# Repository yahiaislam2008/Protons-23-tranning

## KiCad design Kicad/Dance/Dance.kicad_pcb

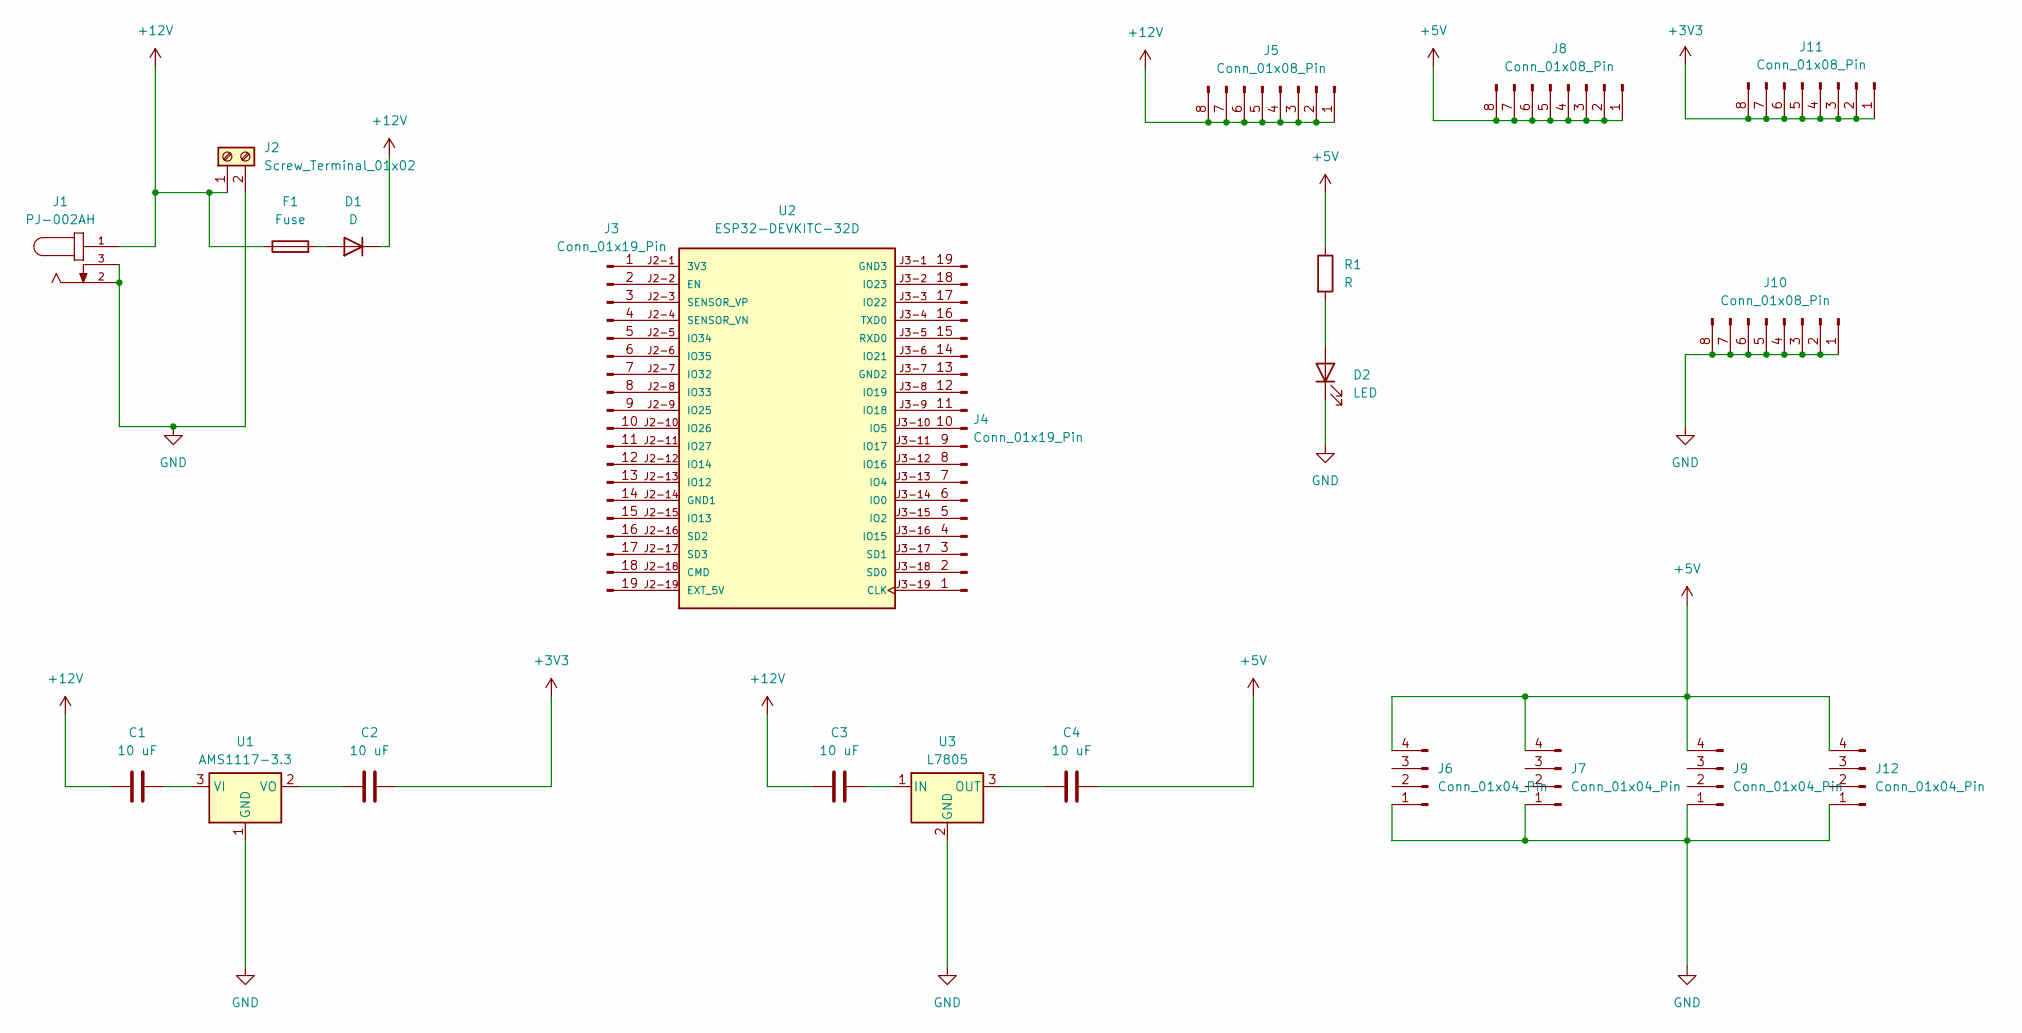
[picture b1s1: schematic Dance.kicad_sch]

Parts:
C1, C2, C3, C4: 10 uF; C_Axial_L3.8mm_D2.6mm_P10.00mm_Horizontal
D1: D; D_5KPW_P12.70mm_Horizontal
D2: LED; LED_D3.0mm
F1: Fuse; Fuse_BelFuse_0ZRE0005FF_L8.3mm_W3.8mm
J1: PJ-002AH; CUI_PJ-002AH
J2: Screw_Terminal_01x02; TerminalBlock_Phoenix_MKDS-1,5-2-5.08_1x02_P5.08mm_Horizont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
J3, J4: Conn_01x19_Pin; PinHeader_1x19_P2.54mm_Vertical
J5, J8, J10, J11: Conn_01x08_Pin; PinHeader_1x08_P2.00mm_Vertical
J6, J7, J9, J12: Conn_01x04_Pin; PinHeader_1x04_P2.00mm_Vertical
R1: R; R_Axial_DIN0207_L6.3mm_D2.5mm_P7.62mm_Horizontal
U1: AMS1117-3.3; SOT-223-3_TabPin2
U2: ESP32-DEVKITC-32D; MODULE_ESP32-DEVKITC-32D; PARTREV V4
U3: L7805; TO-220-3_Vertical

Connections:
+3V3: C2.2, J11.1, J11.2, J11.3, J11.4, J11.5, J11.6, J11.7, J11.8
+5V: C4.2, J6.4, J7.4, J8.1, J8.2, J8.3, J8.4, J8.5, J8.6, J8.7, J8.8, J9.4, J12.4, R1.1
+12V: C1.1, C3.1, D1.1 (K), F1.1, J1.1, J2.1, J5.1, J5.2, J5.3, J5.4, J5.5, J5.6, J5.7, J5.8
GND: D2.1 (K), J1.2, J1.3, J2.2, J6.1, J7.1, J9.1, J10.1, J10.2, J10.3, J10.4, J10.5, J10.6, J10.7, J10.8, J12.1, U1.1 (GND), U3.2 (GND)
unnamed: D1.2 (A), F1.2
unnamed: D2.2 (A), R1.2
unnamed: J3.1, U2.J2-1 (3V3)
unnamed: J3.2, U2.J2-2 (EN)
unnamed: J3.3, U2.J2-3 (SENSOR_VP)
unnamed: J3.4, U2.J2-4 (SENSOR_VN)
unnamed: J3.5, U2.J2-5 (IO34)
unnamed: J3.6, U2.J2-6 (IO35)
unnamed: J3.7, U2.J2-7 (IO32)
unnamed: J3.8, U2.J2-8 (IO33)
unnamed: J3.9, U2.J2-9 (IO25)
unnamed: J3.10, U2.J2-10 (IO26)
unnamed: J3.11, U2.J2-11 (IO27)
unnamed: J3.12, U2.J2-12 (IO14)
unnamed: J3.13, U2.J2-13 (IO12)
unnamed: J3.14, U2.J2-14 (GND1)
unnamed: J3.15, U2.J2-15 (IO13)
unnamed: J3.16, U2.J2-16 (SD2)
unnamed: J3.17, U2.J2-17 (SD3)
unnamed: J3.18, U2.J2-18 (CMD)
unnamed: J3.19, U2.J2-19 (EXT_5V)
unnamed: J4.1, U2.J3-19 (CLK)
unnamed: J4.2, U2.J3-18 (SD0)
unnamed: J4.3, U2.J3-17 (SD1)
unnamed: J4.4, U2.J3-16 (IO15)
unnamed: J4.5, U2.J3-15 (IO2)
unnamed: J4.6, U2.J3-14 (IO0)
unnamed: J4.7, U2.J3-13 (IO4)
unnamed: J4.8, U2.J3-12 (IO16)
unnamed: J4.9, U2.J3-11 (IO17)
unnamed: J4.10, U2.J3-10 (IO5)
unnamed: J4.11, U2.J3-9 (IO18)
unnamed: J4.12, U2.J3-8 (IO19)
unnamed: J4.13, U2.J3-7 (GND2)
unnamed: J4.14, U2.J3-6 (IO21)
unnamed: J4.15, U2.J3-5 (RXD0)
unnamed: J4.16, U2.J3-4 (TXD0)
unnamed: J4.17, U2.J3-3 (IO22)
unnamed: J4.18, U2.J3-2 (IO23)
unnamed: J4.19, U2.J3-1 (GND3)
unnamed: C1.2, U1.3 (VI)
unnamed: C2.1, U1.2 (VO)
unnamed: C3.2, U3.1 (IN)
unnamed: C4.1, U3.3 (OUT)

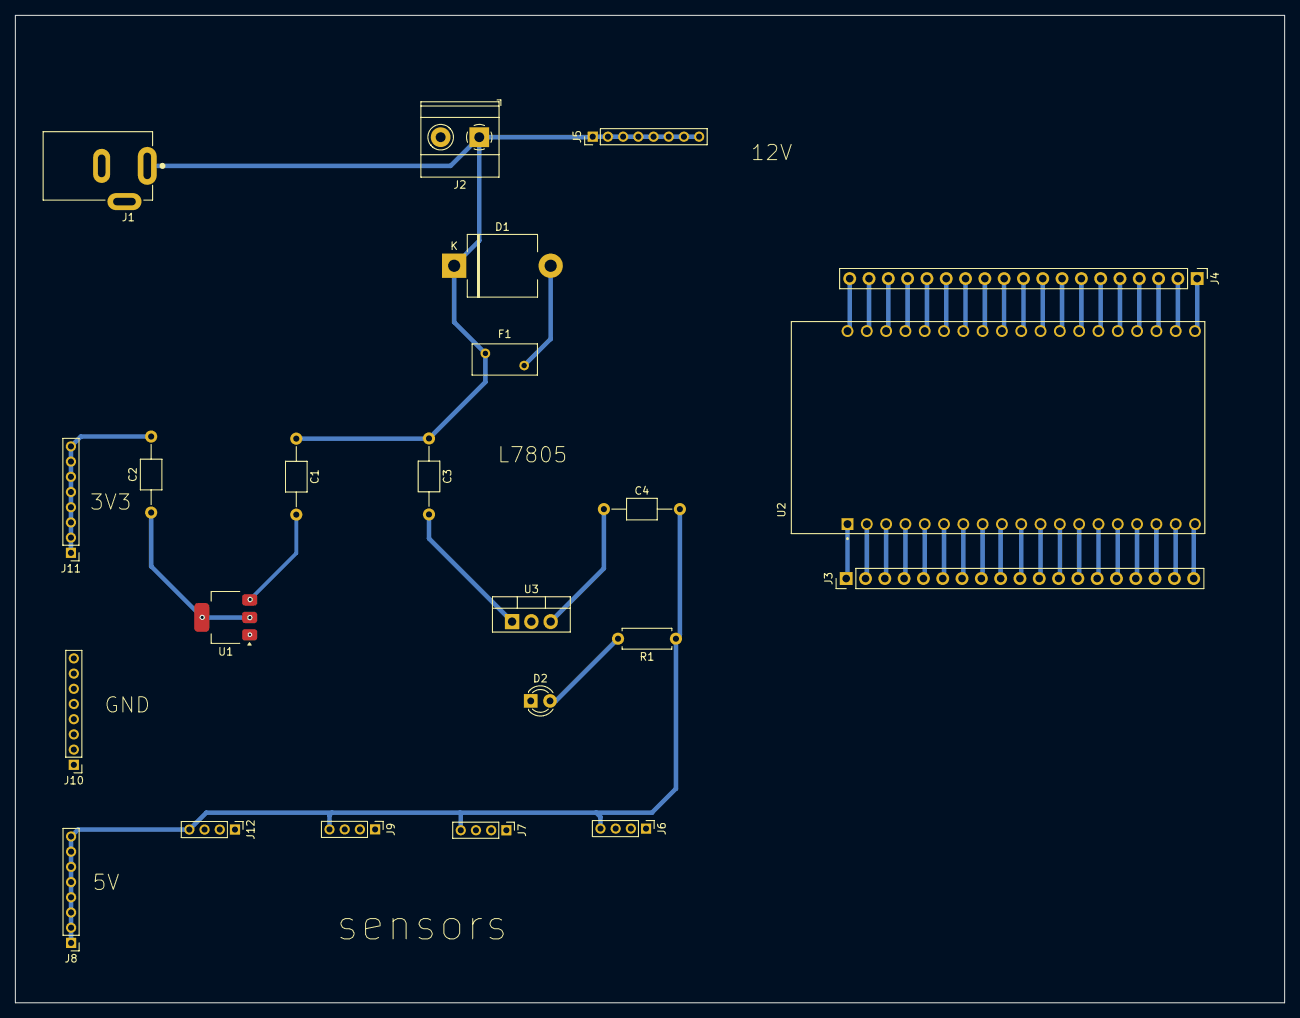
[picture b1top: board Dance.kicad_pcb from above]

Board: 2 copper layers, 167.0 x 129.9 mm, 23 parts (0 on the bottom side), 48 nets.

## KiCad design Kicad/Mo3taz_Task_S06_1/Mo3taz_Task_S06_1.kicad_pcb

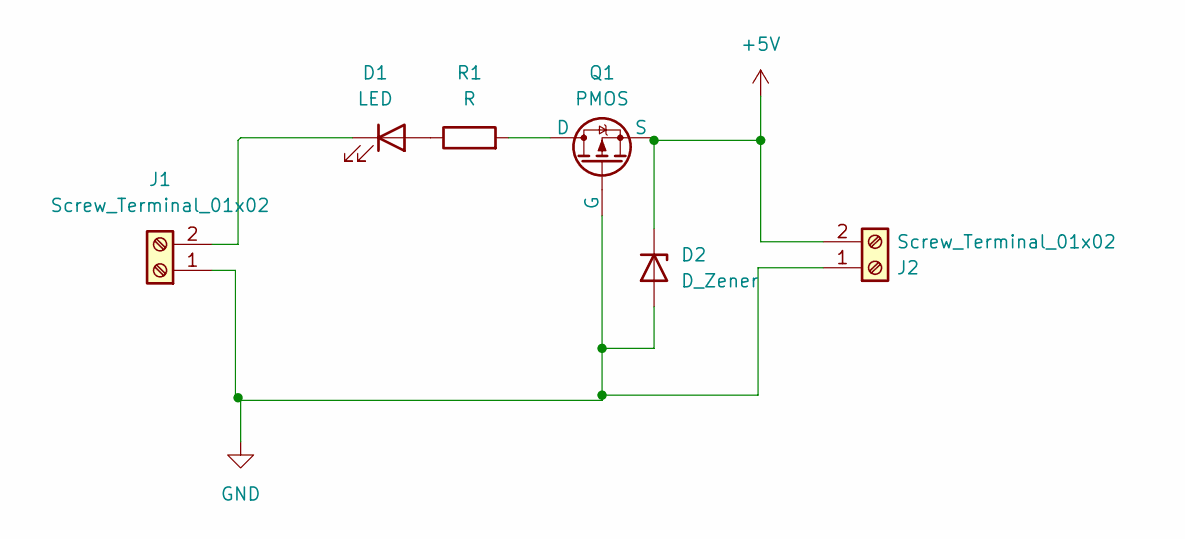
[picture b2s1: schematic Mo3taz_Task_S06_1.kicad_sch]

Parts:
D1: LED; LED_0603_1608Metric
D2: D_Zener; D_0603_1608Metric
J1, J2: Screw_Terminal_01x02; TerminalBlock_Phoenix_MKDS-1,5-2-5.08_1x02_P5.08mm_Horizont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
Q1: PMOS; GaN_Systems_GaNPX-3_5x6.6mm_Drain2.93x0.6mm
R1: R; R_0603_1608Metric

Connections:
+5V: D2.1 (K), J2.2, Q1.3 (S)
GND: D2.2 (A), J1.1, J2.1, Q1.2 (G)
unnamed: D1.2 (A), R1.1
unnamed: D1.1 (K), J1.2
unnamed: Q1.1 (D), R1.2

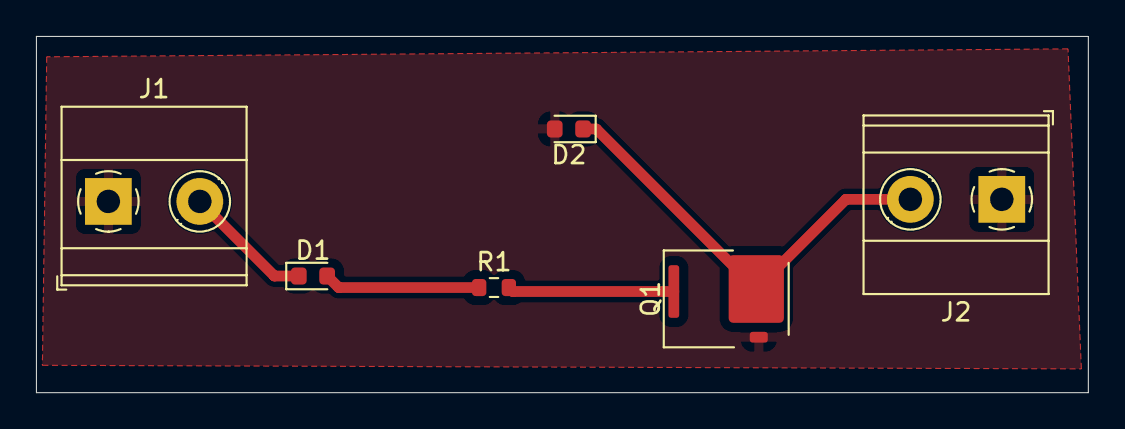
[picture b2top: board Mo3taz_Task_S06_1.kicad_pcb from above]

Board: 2 copper layers, 58.4 x 19.8 mm, 6 parts (0 on the bottom side), 5 nets.

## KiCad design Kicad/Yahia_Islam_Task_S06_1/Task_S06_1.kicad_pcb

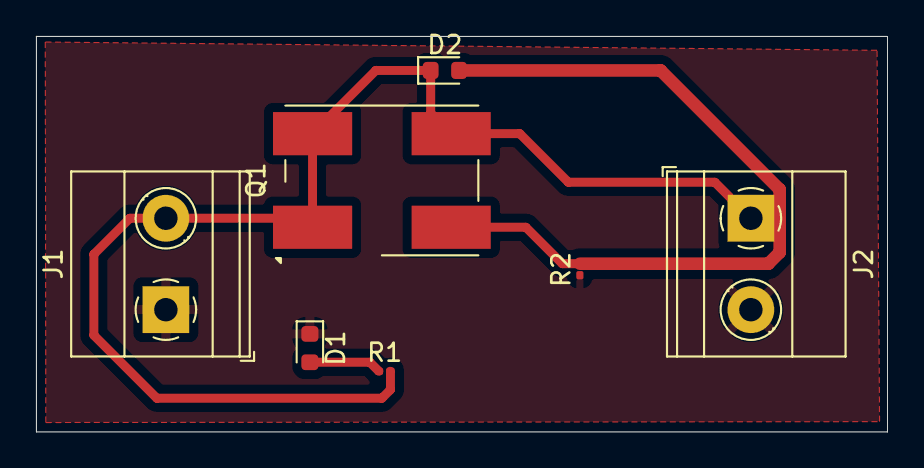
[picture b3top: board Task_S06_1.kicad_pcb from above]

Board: 2 copper layers, 47.3 x 22.0 mm, 7 parts (0 on the bottom side), 4 nets.

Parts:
D1: LED; LED_0603_1608Metric
D2: D; D_0603_1608Metric
J1, J2: Screw_Terminal_01x02; TerminalBlock_Phoenix_MKDS-1,5-2-5.08_1x02_P5.08mm_Horizont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
Q1: PMOS_Substrate; Diode_Bridge_Bourns_CD-DF4xxS
R1, R2: 330R; R_0201_0603Metric

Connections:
+9V: D2.1 (K), J1.2, J2.1, Q1.1 (D), Q1.3 (S), Q1.4 (Bulk), R1.2
GND: D1.1 (K), J1.1, J2.2, R2.1
unnamed: D1.2 (A), R1.1
unnamed: D2.2 (A), Q1.2 (G), R2.2

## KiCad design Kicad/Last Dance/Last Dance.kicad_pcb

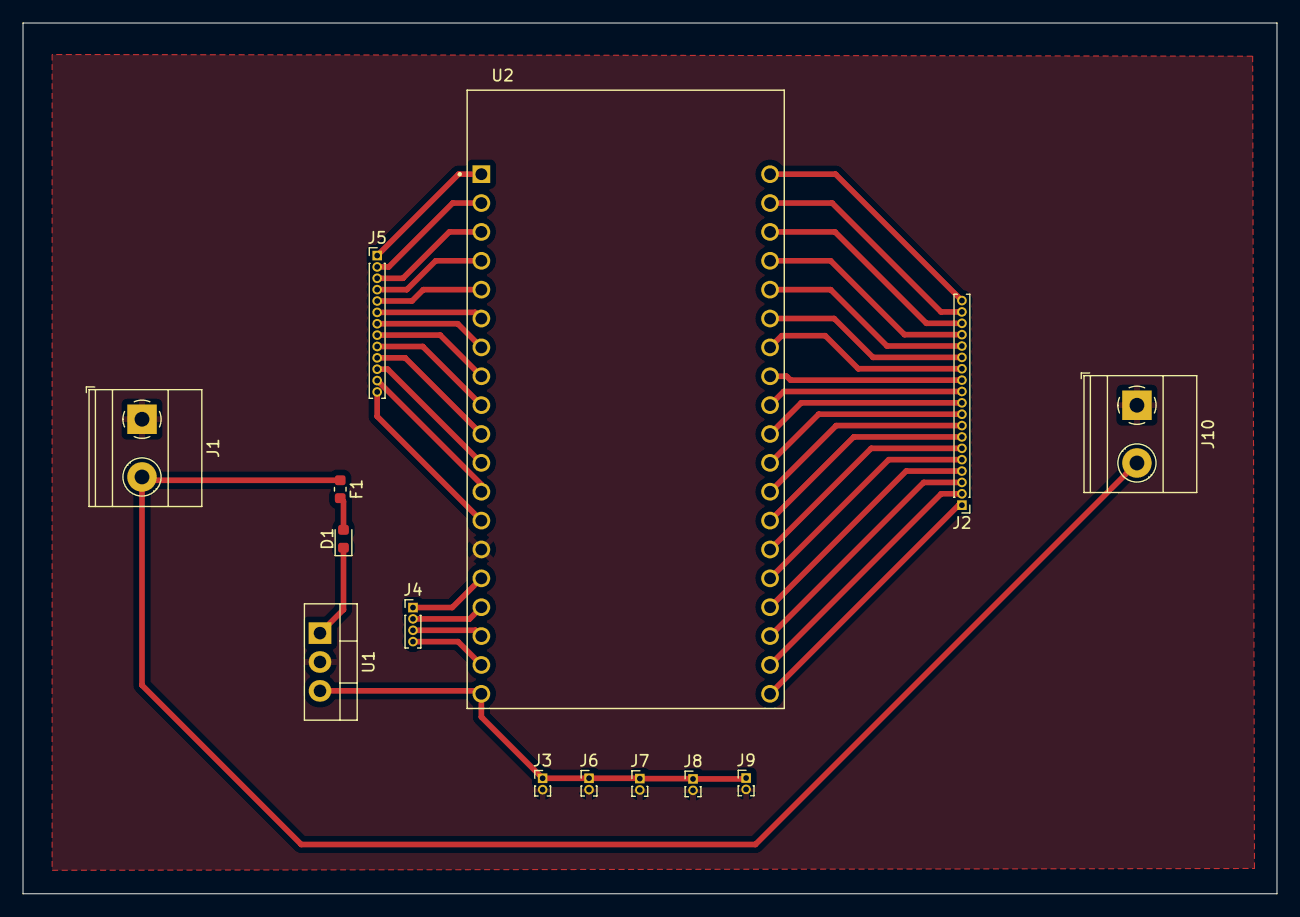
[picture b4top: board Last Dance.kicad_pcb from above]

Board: 2 copper layers, 110.3 x 76.6 mm, 14 parts (0 on the bottom side), 41 nets.

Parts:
D1: D; D_0603_1608Metric
F1: Fuse; Fuse_0603_1608Metric
J1, J10: Screw_Terminal_01x02; TerminalBlock_Phoenix_MKDS-1,5-2-5.08_1x02_P5.08mm_Horizont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
J2: Conn_01x19_Pin; PinHeader_1x19_P1.00mm_Vertical
J3, J6, J7, J8, J9: Conn_01x02_Pin; PinHeader_1x02_P1.00mm_Vertical
J4: Conn_01x04_Pin; PinHeader_1x04_P1.00mm_Vertical
J5: Conn_01x13_Pin; PinHeader_1x13_P1.00mm_Vertical
U1: LM7805_TO220; TO-220-3_Vertical
U2: ESP32-DEVKITC-32D; MODULE_ESP32-DEVKITC-32D

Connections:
+12V: F1.1, J1.2, J10.2
GND: J1.1, J3.2, J6.2, J7.2, J8.2, J9.2, J10.1, U1.2 (GND), U2.J2-14 (GND1)
unnamed: D1.2 (A), F1.2
unnamed: D1.1 (K), U1.1 (VI)
unnamed: J2.1, U2.J3-19 (CLK)
unnamed: J2.2, U2.J3-18 (SD0)
unnamed: J2.3, U2.J3-17 (SD1)
unnamed: J2.4, U2.J3-16 (IO15)
unnamed: J2.5, U2.J3-15 (IO2)
unnamed: J2.6, U2.J3-14 (IO0)
unnamed: J2.7, U2.J3-13 (IO4)
unnamed: J2.8, U2.J3-12 (IO16)
unnamed: J2.9, U2.J3-11 (IO17)
unnamed: J2.10, U2.J3-10 (IO5)
unnamed: J2.11, U2.J3-9 (IO18)
unnamed: J2.12, U2.J3-8 (IO19)
unnamed: J2.13, U2.J3-7 (GND2)
unnamed: J2.14, U2.J3-6 (IO21)
unnamed: J2.15, U2.J3-5 (RXD0)
unnamed: J2.16, U2.J3-4 (TXD0)
unnamed: J2.17, U2.J3-3 (IO22)
unnamed: J2.18, U2.J3-2 (IO23)
unnamed: J2.19, U2.J3-1 (GND3)
unnamed: J3.1, J6.1, J7.1, J8.1, J9.1, U1.3 (VO), U2.J2-19 (EXT_5V)
unnamed: J4.1, U2.J2-15 (IO13)
unnamed: J4.2, U2.J2-16 (SD2)
unnamed: J4.3, U2.J2-17 (SD3)
unnamed: J4.4, U2.J2-18 (CMD)
unnamed: J5.1, U2.J2-1 (3V3)
unnamed: J5.2, U2.J2-2 (EN)
unnamed: J5.3, U2.J2-3 (SENSOR_VP)
unnamed: J5.4, U2.J2-4 (SENSOR_VN)
unnamed: J5.5, U2.J2-5 (IO34)
unnamed: J5.6, U2.J2-6 (IO35)
unnamed: J5.7, U2.J2-7 (IO32)
unnamed: J5.8, U2.J2-8 (IO33)
unnamed: J5.9, U2.J2-9 (IO25)
unnamed: J5.10, U2.J2-10 (IO26)
unnamed: J5.11, U2.J2-11 (IO27)
unnamed: J5.12, U2.J2-12 (IO14)
unnamed: J5.13, U2.J2-13 (IO12)

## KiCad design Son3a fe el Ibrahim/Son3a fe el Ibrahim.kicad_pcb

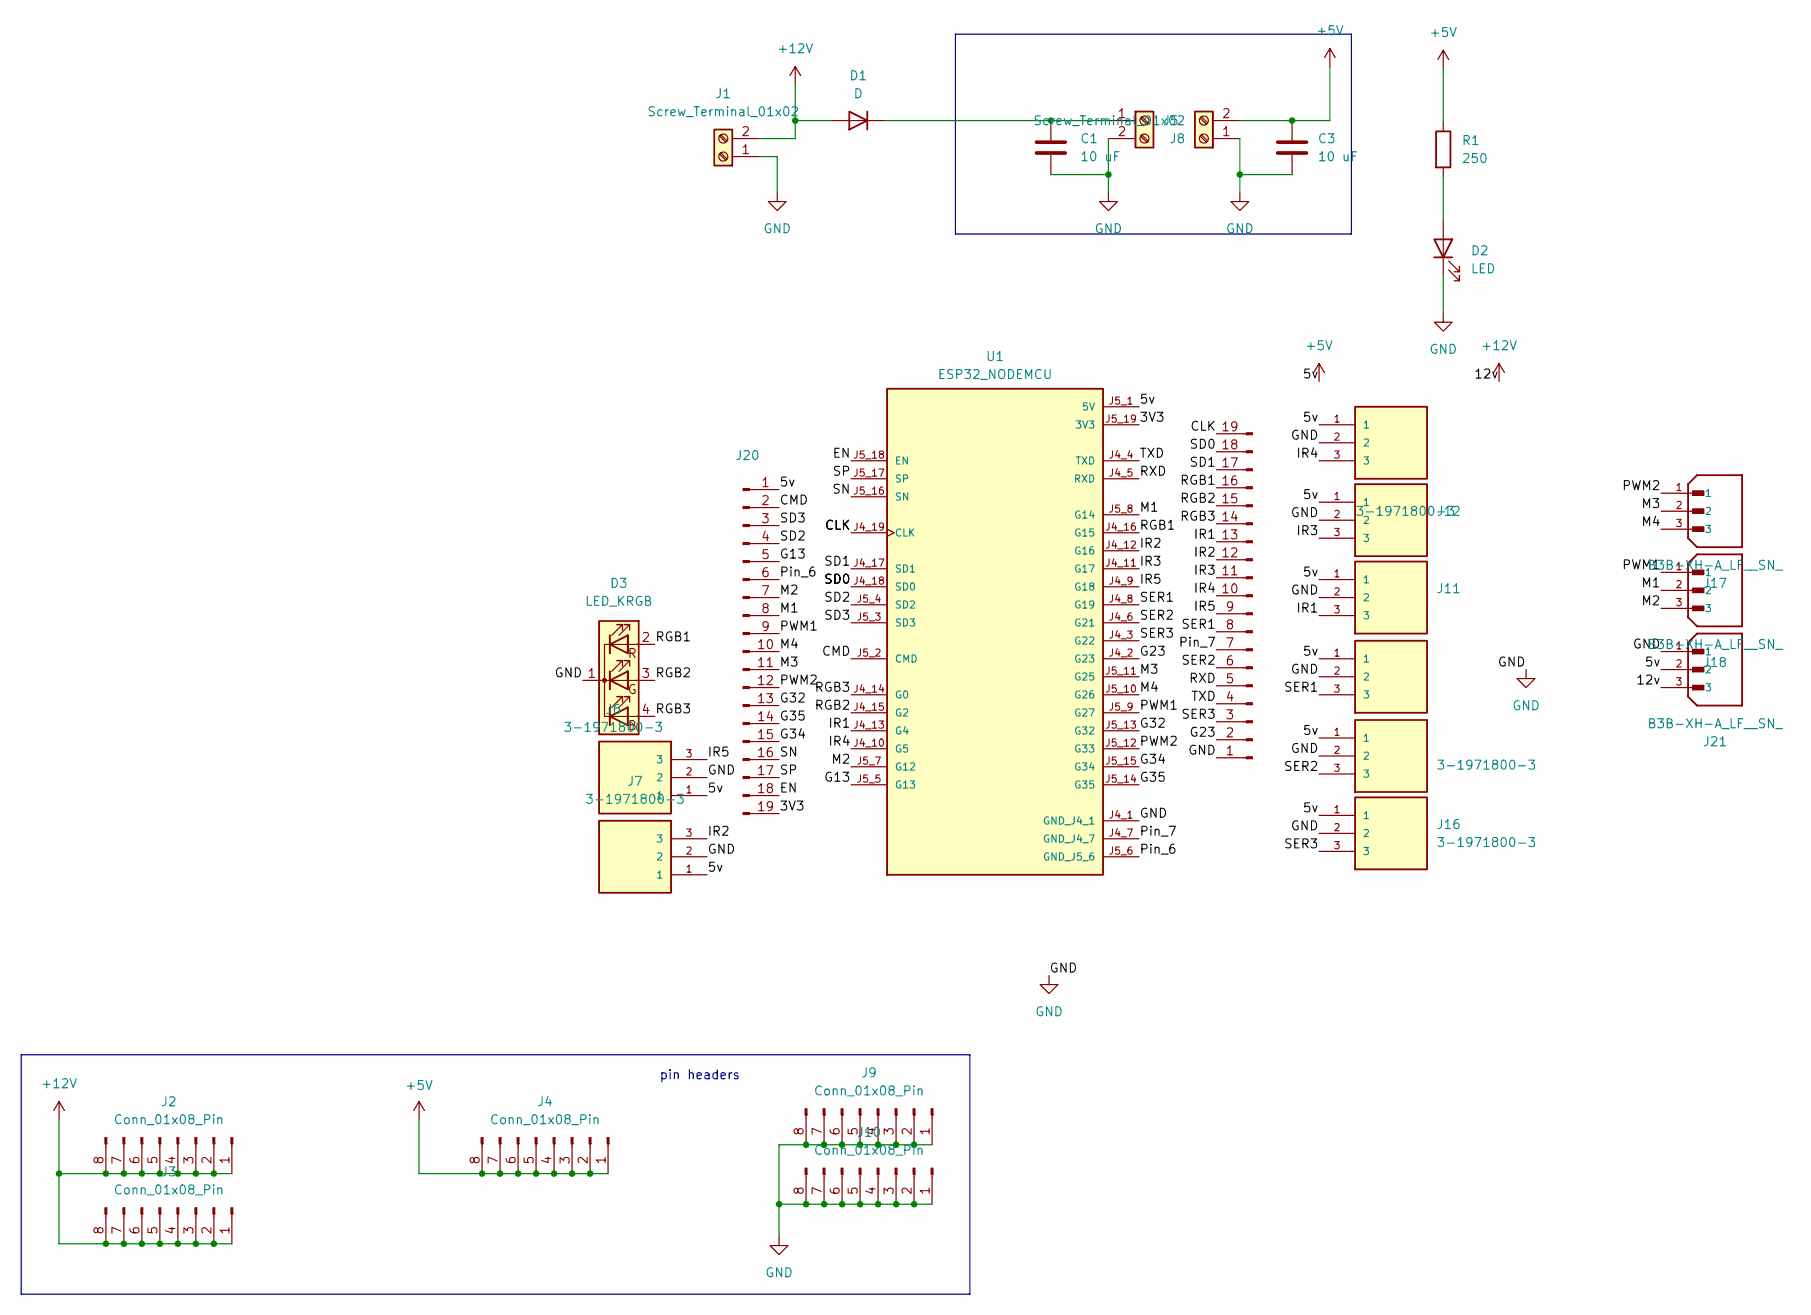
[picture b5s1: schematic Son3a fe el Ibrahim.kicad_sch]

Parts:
C1, C3: 10 uF; C_0805_2012Metric
D1: D; D_1210_3225Metric
D2: LED; LED_D3.0mm
D3: LED_KRGB; LED_D5.0mm-4_RGB_Wide_Pins
J1, J5, J8: Screw_Terminal_01x02; TerminalBlock_Phoenix_MKDS-1,5-2-5.08_1x02_P5.08mm_Horizont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
J2, J3, J4, J9, J10: Conn_01x08_Pin; PinHeader_1x08_P2.54mm_Vertical
J6, J7, J11, J12, J13, J14, J15, J16: 3-1971800-3; TE_3-1971800-3
J17, J18, J21: B3B-XH-A_LF__SN_; JST_B3B-XH-A_LF__SN_; PARTREV 7/4/21
J19, J20: Conn_01x19_Pin; PinHeader_1x19_P2.54mm_Vertical
R1: 250; R_Axial_DIN0207_L6.3mm_D2.5mm_P7.62mm_Horizontal
U1: ESP32_NODEMCU; MODULE_ESP32_NODEMCU

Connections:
+5V: C3.2, J4.1, J4.2, J4.3, J4.4, J4.5, J4.6, J4.7, J4.8, J6.1, J7.1, J8.2, J11.1, J12.1, J13.1, J14.1, J15.1, J16.1, J20.1, J21.2, R1.1, U1.J5_1 (5V)
+12V: D1.2 (A), J1.2, J2.1, J2.2, J2.3, J2.4, J2.5, J2.6, J2.7, J2.8, J3.1, J3.2, J3.3, J3.4, J3.5, J3.6, J3.7, J3.8, J21.3
/3V3: J20.19, U1.J5_19 (3V3)
/CLK: J19.19, U1.J4_19 (CLK)
/CMD: J20.2, U1.J5_2 (CMD)
/EN: J20.18, U1.J5_18 (EN)
/G13: J20.5, U1.J5_5 (G13)
/G23: J19.2, U1.J4_2 (G23)
/G32: J20.13, U1.J5_13 (G32)
/G34: J20.15, U1.J5_15 (G34)
/G35: J20.14, U1.J5_14 (G35)
/IR1: J11.3, J19.13, U1.J4_13 (G4)
/IR2: J7.3, J19.12, U1.J4_12 (G16)
/IR3: J12.3, J19.11, U1.J4_11 (G17)
/IR4: J13.3, J19.10, U1.J4_10 (G5)
/IR5: J6.3, J19.9, U1.J4_9 (G18)
/M1: J18.2, J20.8, U1.J5_8 (G14)
/M2: J18.3, J20.7, U1.J5_7 (G12)
/M3: J17.2, J20.11, U1.J5_11 (G25)
/M4: J17.3, J20.10, U1.J5_10 (G26)
/PWM1: J18.1, J20.9, U1.J5_9 (G27)
/PWM2: J17.1, J20.12, U1.J5_12 (G33)
/Pin_6: J20.6, U1.J5_6 (GND_J5_6)
/Pin_7: J19.7, U1.J4_7 (GND_J4_7)
/RGB1: D3.2 (RA), J19.16, U1.J4_16 (G15)
/RGB2: D3.3 (GA), J19.15, U1.J4_15 (G2)
/RGB3: D3.4 (BA), J19.14, U1.J4_14 (G0)
/RXD: J19.5, U1.J4_5 (RXD)
/SD0: J19.18, U1.J4_18 (SD0)
/SD1: J19.17, U1.J4_17 (SD1)
/SD2: J20.4, U1.J5_4 (SD2)
/SD3: J20.3, U1.J5_3 (SD3)
/SER1: J14.3, J19.8, U1.J4_8 (G19)
/SER2: J15.3, J19.6, U1.J4_6 (G21)
/SER3: J16.3, J19.3, U1.J4_3 (G22)
/SN: J20.16, U1.J5_16 (SN)
/SP: J20.17, U1.J5_17 (SP)
/TXD: J19.4, U1.J4_4 (TXD)
GND: C1.2, C3.1, D2.1 (K), D3.1 (K), J1.1, J5.2, J6.2, J7.2, J8.1, J9.1, J9.2, J9.3, J9.4, J9.5, J9.6, J9.7, J9.8, J10.1, J10.2, J10.3, J10.4, J10.5, J10.6, J10.7, J10.8, J11.2, J12.2, J13.2, J14.2, J15.2, J16.2, J19.1, J21.1, U1.J4_1 (GND_J4_1)
unnamed: C1.1, D1.1 (K), J5.1
unnamed: D2.2 (A), R1.2

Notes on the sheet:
pin headers

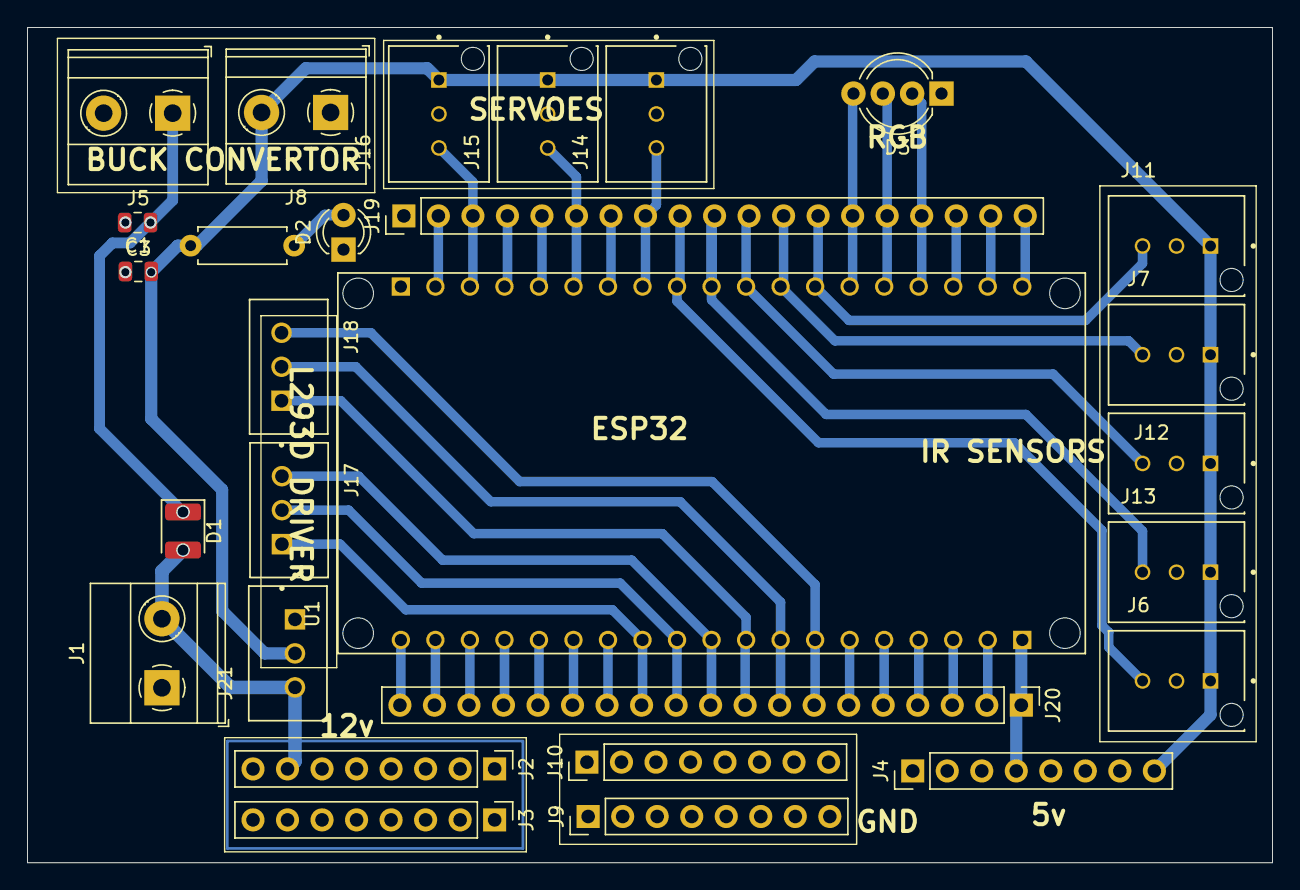
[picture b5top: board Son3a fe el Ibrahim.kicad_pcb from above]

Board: 2 copper layers, 91.6 x 61.5 mm, 28 parts (0 on the bottom side), 41 nets.

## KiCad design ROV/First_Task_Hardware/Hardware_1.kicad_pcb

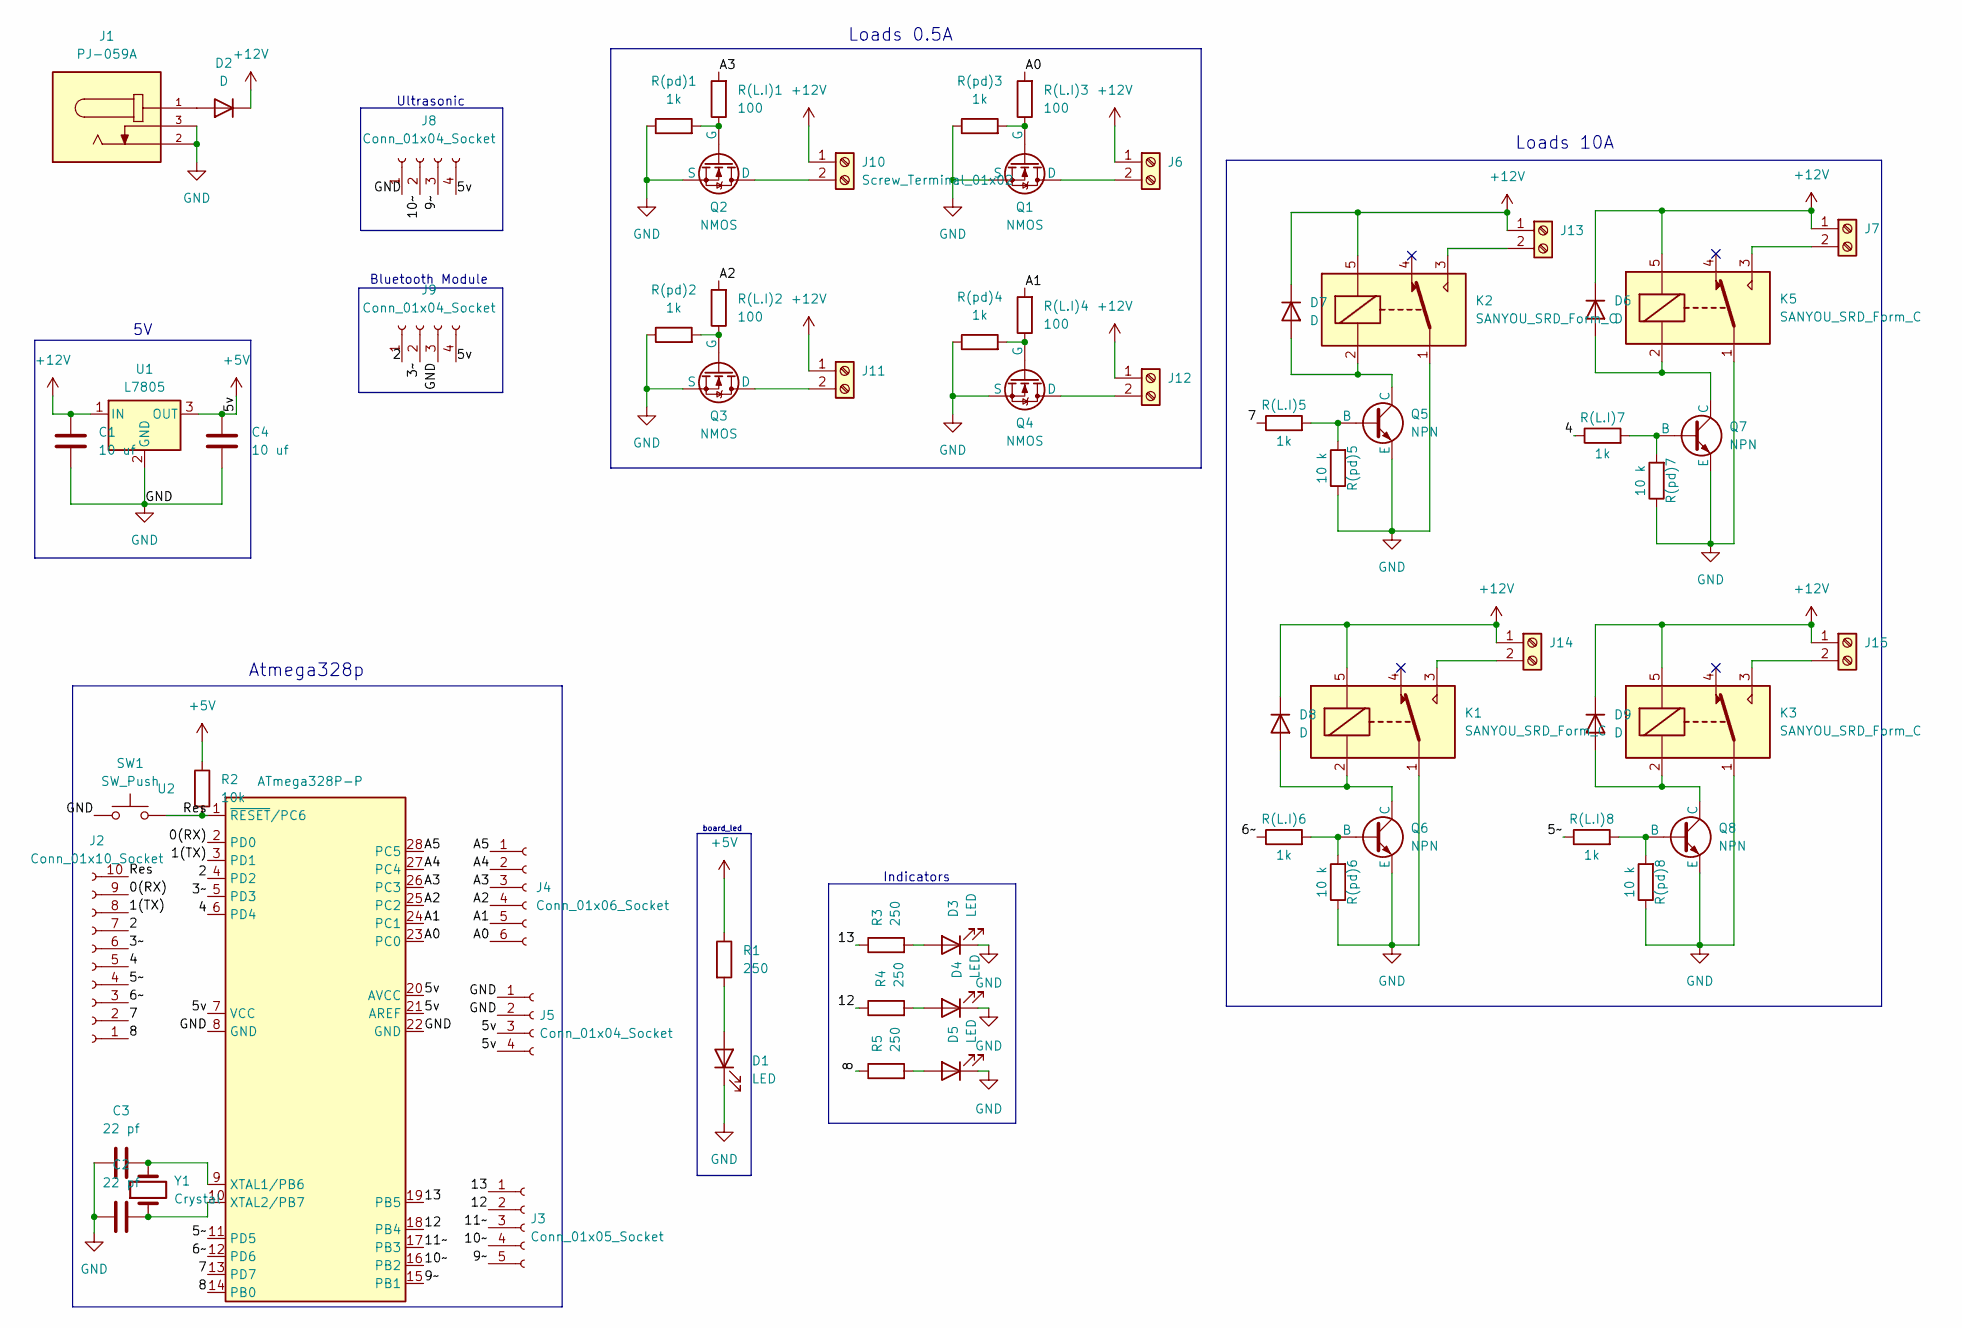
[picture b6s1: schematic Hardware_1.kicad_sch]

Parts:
C1, C4: 10 uf; C_Radial_D4.0mm_H5.0mm_P1.50mm
C2, C3: 22 pf; C_Disc_D3.0mm_W1.6mm_P2.50mm
D1, D3, D4, D5: LED; LED_D3.0mm
D2, D6, D7, D8, D9: D; D_DO-34_SOD68_P7.62mm_Horizontal
J1: PJ-059A; CUI_PJ-059A; PARTREV 1.04; DigiKey_Part_Number CP-059A-ND
J2: Conn_01x10_Socket; PinSocket_1x10_P2.54mm_Vertical
J3: Conn_01x05_Socket; PinSocket_1x05_P2.54mm_Vertical
J4: Conn_01x06_Socket; PinSocket_1x06_P2.54mm_Vertical
J5, J8, J9: Conn_01x04_Socket; PinSocket_1x04_P2.54mm_Vertical
J6, J7, J10, J11, J12, J13, J14, J15: Screw_Terminal_01x02; TerminalBlock_Phoenix_MKDS-1,5-2_1x02_P5.00mm_Horizontal
K1, K2, K3, K5: SANYOU_SRD_Form_C; Relay_SPDT_SANYOU_SRD_Series_Form_C
Q1, Q2, Q3, Q4: NMOS; JST_B3B-XH-A_LF__SN_
Q5, Q6, Q7, Q8: NPN; JST_B3B-XH-A_LF__SN_
R1, R3, R4, R5: 250; R_Axial_DIN0204_L3.6mm_D1.6mm_P5.08mm_Horizontal
R2: 10k; R_Axial_DIN0204_L3.6mm_D1.6mm_P7.62mm_Horizontal
R(L.I)1, R(L.I)2, R(L.I)3, R(L.I)4: 100; R_Axial_DIN0204_L3.6mm_D1.6mm_P5.08mm_Horizontal
R(L.I)5, R(L.I)6, R(L.I)7, R(L.I)8: 1k; R_Axial_DIN0204_L3.6mm_D1.6mm_P5.08mm_Horizontal
R(pd)1, R(pd)2, R(pd)3, R(pd)4: 1k; R_Axial_DIN0204_L3.6mm_D1.6mm_P5.08mm_Horizontal
R(pd)5, R(pd)6, R(pd)7, R(pd)8: 10 k; R_Axial_DIN0204_L3.6mm_D1.6mm_P5.08mm_Horizontal
SW1: SW_Push; SW_PUSH_6mm
U1: L7805; TO-220-3_Vertical
U2: ATmega328P-P; DIP-28_W7.62mm
Y1: Crystal; Crystal_HC52-6mm_Vertical

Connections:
+5V: C4.1, J5.3, J5.4, J8.4, J9.4, R1.1, R2.1, U1.3 (OUT), U2.7 (VCC), U2.20 (AVCC), U2.21 (AREF)
+12V: C1.1, D2.1 (K), D6.1 (K), D7.1 (K), D8.1 (K), D9.1 (K), J6.1, J7.1, J10.1, J11.1, J12.1, J13.1, J14.1, J15.1, K1.5, K2.5, K3.5, K5.5, U1.1 (IN)
/0(RX): J2.9, U2.2 (PD0)
/1(TX): J2.8, U2.3 (PD1)
/2: J2.7, J9.1, U2.4 (PD2)
/3~: J2.6, J9.2, U2.5 (PD3)
/4: J2.5, R(L.I)7.1, U2.6 (PD4)
/5~: J2.4, R(L.I)8.1, U2.11 (PD5)
/6~: J2.3, R(L.I)6.1, U2.12 (PD6)
/7: J2.2, R(L.I)5.1, U2.13 (PD7)
/8: J2.1, R5.1, U2.14 (PB0)
/9~: J3.5, J8.3, U2.15 (PB1)
/10~: J3.4, J8.2, U2.16 (PB2)
/11~: J3.3, U2.17 (PB3)
/12: J3.2, R4.1, U2.18 (PB4)
/13: J3.1, R3.1, U2.19 (PB5)
/A0: J4.6, R(L.I)3.2, U2.23 (PC0)
/A1: J4.5, R(L.I)4.2, U2.24 (PC1)
/A2: J4.4, R(L.I)2.2, U2.25 (PC2)
/A3: J4.3, R(L.I)1.2, U2.26 (PC3)
/A4: J4.2, U2.27 (PC4)
/A5: J4.1, U2.28 (PC5)
/Res: J2.10, R2.2, SW1.2, U2.1 (~RESET/PC6)
GND: C1.2, C2.1, C3.1, C4.2, D1.1 (K), D3.1 (K), D4.1 (K), D5.1 (K), J1.2, J1.3, J5.1, J5.2, J8.1, J9.3, K1.1, K2.1, K3.1, K5.1, Q1.3 (S), Q2.3 (S), Q3.3 (S), Q4.3 (S), Q5.3 (E), Q6.3 (E), Q7.3 (E), Q8.3 (E), R(pd)1.1, R(pd)2.1, R(pd)3.1, R(pd)4.1, R(pd)5.1, R(pd)6.1, R(pd)7.1, R(pd)8.1, SW1.1, U1.2 (GND), U2.8 (GND), U2.22 (GND)
unnamed: D1.2 (A), R1.2
unnamed: D2.2 (A), J1.1
unnamed: D3.2 (A), R3.2
unnamed: D4.2 (A), R4.2
unnamed: D5.2 (A), R5.2
unnamed: D6.2 (A), K5.2, Q7.1 (C)
unnamed: D7.2 (A), K2.2, Q5.1 (C)
unnamed: D8.2 (A), K1.2, Q6.1 (C)
unnamed: D9.2 (A), K3.2, Q8.1 (C)
unnamed: J6.2, Q1.1 (D)
unnamed: J7.2, K5.3
unnamed: J10.2, Q2.1 (D)
unnamed: J11.2, Q3.1 (D)
unnamed: J12.2, Q4.1 (D)
unnamed: J13.2, K2.3
unnamed: J14.2, K1.3
unnamed: J15.2, K3.3
unnamed: Q1.2 (G), R(L.I)3.1, R(pd)3.2
unnamed: Q2.2 (G), R(L.I)1.1, R(pd)1.2
unnamed: Q3.2 (G), R(L.I)2.1, R(pd)2.2
unnamed: Q4.2 (G), R(L.I)4.1, R(pd)4.2
unnamed: Q5.2 (B), R(L.I)5.2, R(pd)5.2
unnamed: Q6.2 (B), R(L.I)6.2, R(pd)6.2
unnamed: Q7.2 (B), R(L.I)7.2, R(pd)7.2
unnamed: Q8.2 (B), R(L.I)8.2, R(pd)8.2
unnamed: C3.2, U2.9 (XTAL1/PB6), Y1.2
unnamed: C2.2, U2.10 (XTAL2/PB7), Y1.1

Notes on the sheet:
Atmega328p
Bluetooth Module
Indicators
Loads 0.5A
Ultrasonic
board_led
Loads 10A

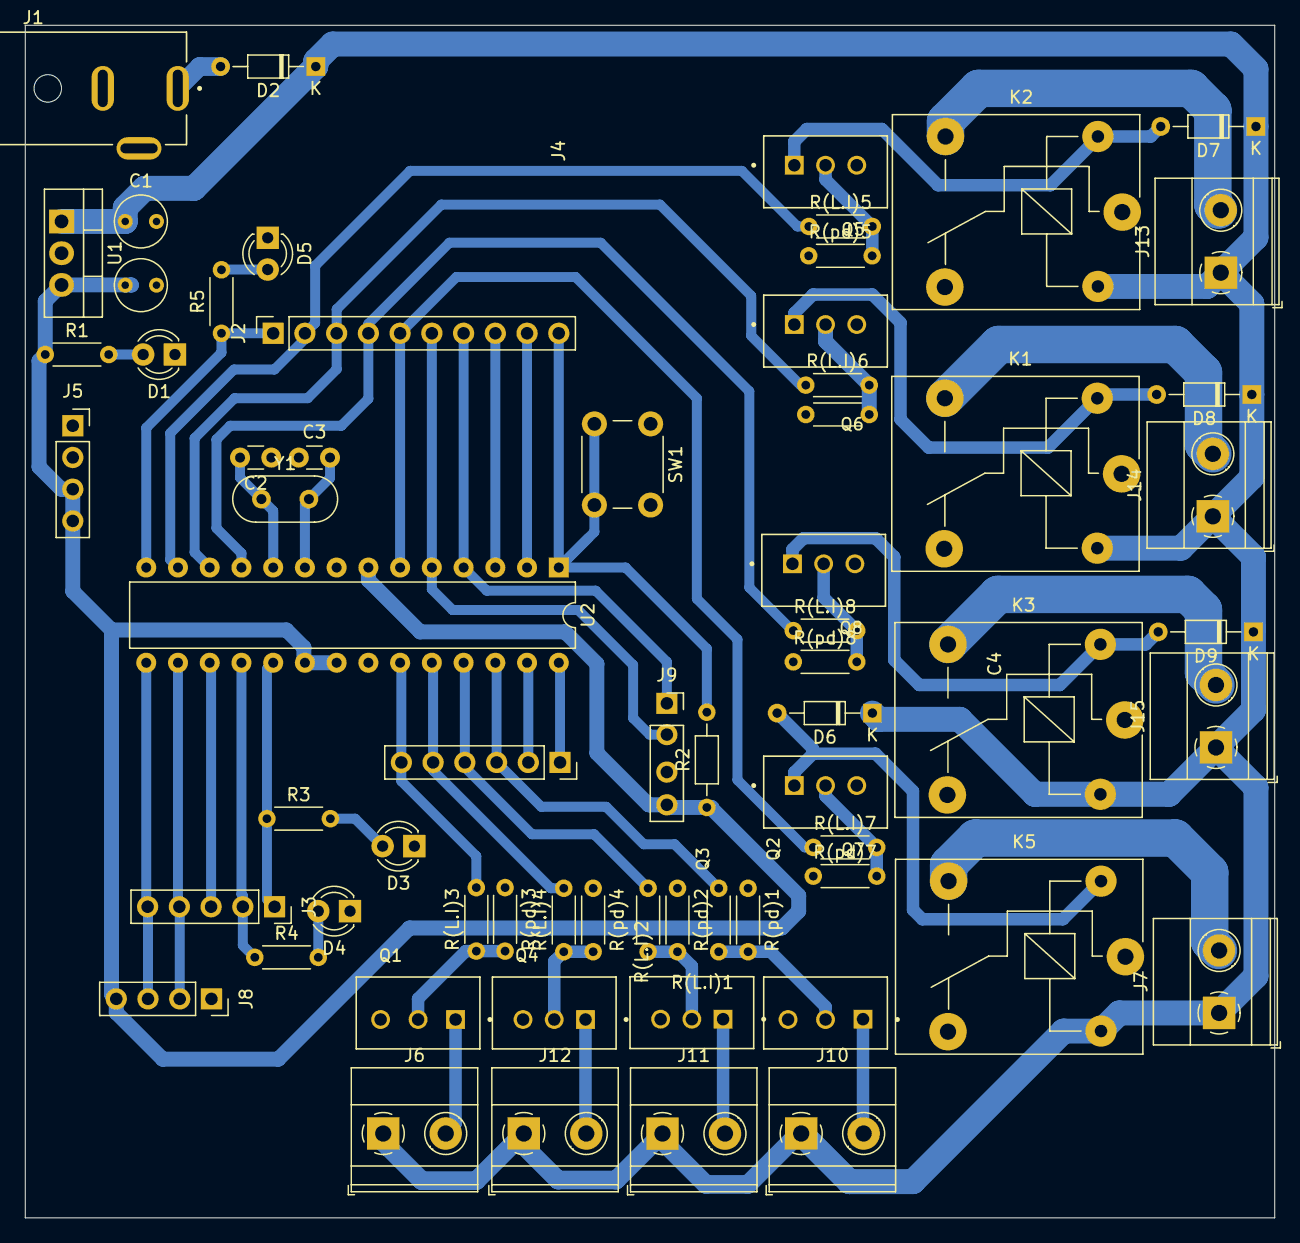
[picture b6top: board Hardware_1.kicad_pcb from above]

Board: 2 copper layers, 100.0 x 95.5 mm, 65 parts (0 on the bottom side), 51 nets.

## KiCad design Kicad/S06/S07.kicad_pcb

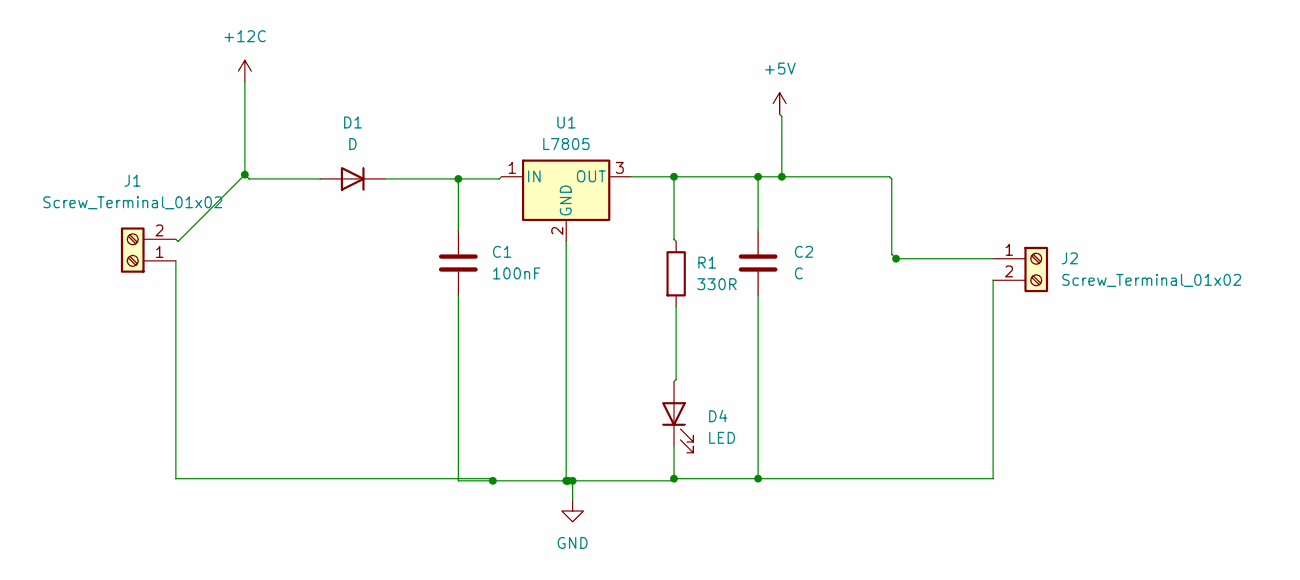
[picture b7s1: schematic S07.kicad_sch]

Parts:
C1: 100nF; C_0603_1608Metric
C2: C; C_0603_1608Metric
D1: D; D_0603_1608Metric
D4: LED; LED_0603_1608Metric
J1, J2: Screw_Terminal_01x02; TerminalBlock_Phoenix_MKDS-1,5-2-5.08_1x02_P5.08mm_Horizont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
R1: 330R; R_0201_0603Metric
U1: L7805; TO-252-2

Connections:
+5V: C2.1, J2.1, R1.1, U1.3 (OUT)
+12C: D1.2 (A), J1.2
GND: C1.2, C2.2, D4.1 (K), J1.1, J2.2, U1.2 (GND)
unnamed: C1.1, D1.1 (K), U1.1 (IN)
unnamed: D4.2 (A), R1.2

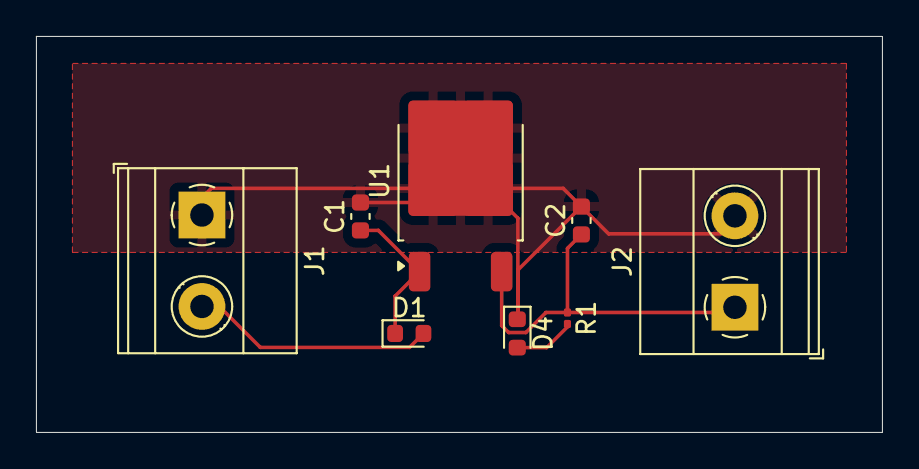
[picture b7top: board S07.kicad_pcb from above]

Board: 2 copper layers, 47.0 x 22.0 mm, 8 parts (0 on the bottom side), 5 nets.
